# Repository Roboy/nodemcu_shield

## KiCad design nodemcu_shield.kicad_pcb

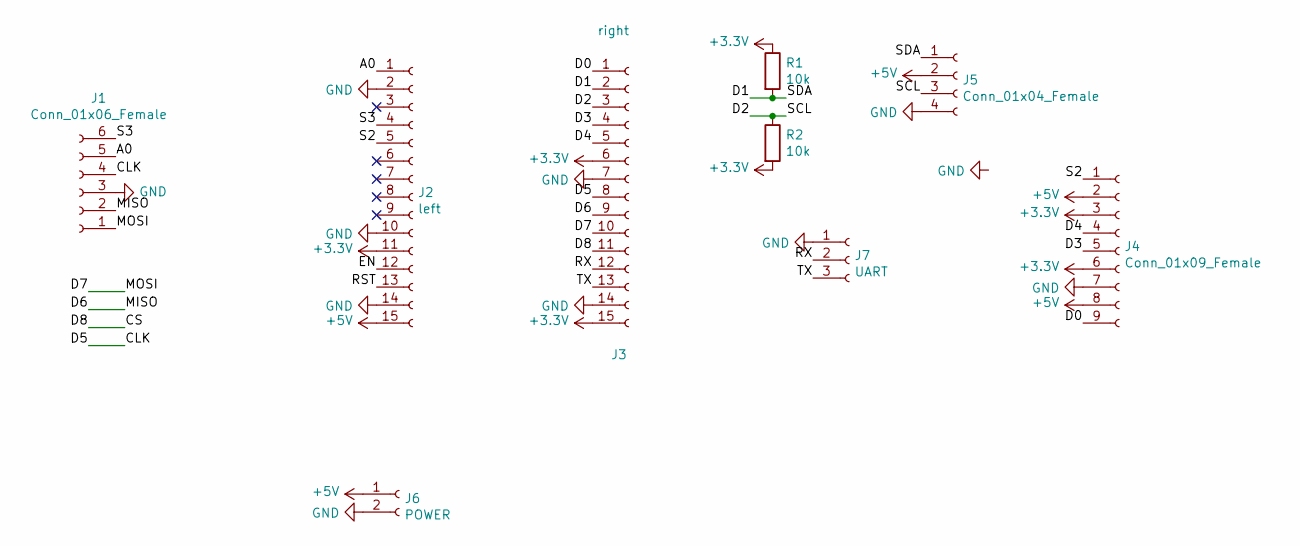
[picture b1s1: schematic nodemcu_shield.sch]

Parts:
J1: Conn_01x06_Female; TE-Connectivity_Micro-Match_connector_02x03_Pitch_1.27mm
J2: left; PinSocket_1x15_P2.54mm_Vertical
J3: right; PinSocket_1x15_P2.54mm_Vertical
J4: Conn_01x09_Female; PinHeader_1x09_P2.54mm_Horizontal
J5: Conn_01x04_Female; TE-Connectivity_Micro-Match_connector_02x02_Pitch_1.27mm
J6: POWER; Wago_2060_2_SMD
J7: UART; PinHeader_1x03_P2.54mm_Horizontal
R1, R2: 10k; R_0402_1005Metric

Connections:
+3V3: J2.11, J3.6, J3.15, J4.3, J4.6, R1.1, R2.2
+5V: J2.15, J4.2, J4.8, J5.2, J6.1
/A0: J1.5, J2.1
/CLK: J1.4, J3.8
/CS: J3.11
/D0: J3.1, J4.9
/D1: J3.2, J5.1, R1.2
/D2: J3.3, J5.3, R2.1
/D3: J3.4, J4.5
/D4: J3.5, J4.4
/D6: J1.2, J3.9
/D7: J1.1, J3.10
/EN: J2.12
/RST: J2.13
/RX: J3.12, J7.2
/S2: J2.5, J4.1
/S3: J1.6, J2.4
/TX: J3.13, J7.3
GND: J1.3, J2.2, J2.10, J2.14, J3.7, J3.14, J4.7, J5.4, J6.2, J7.1

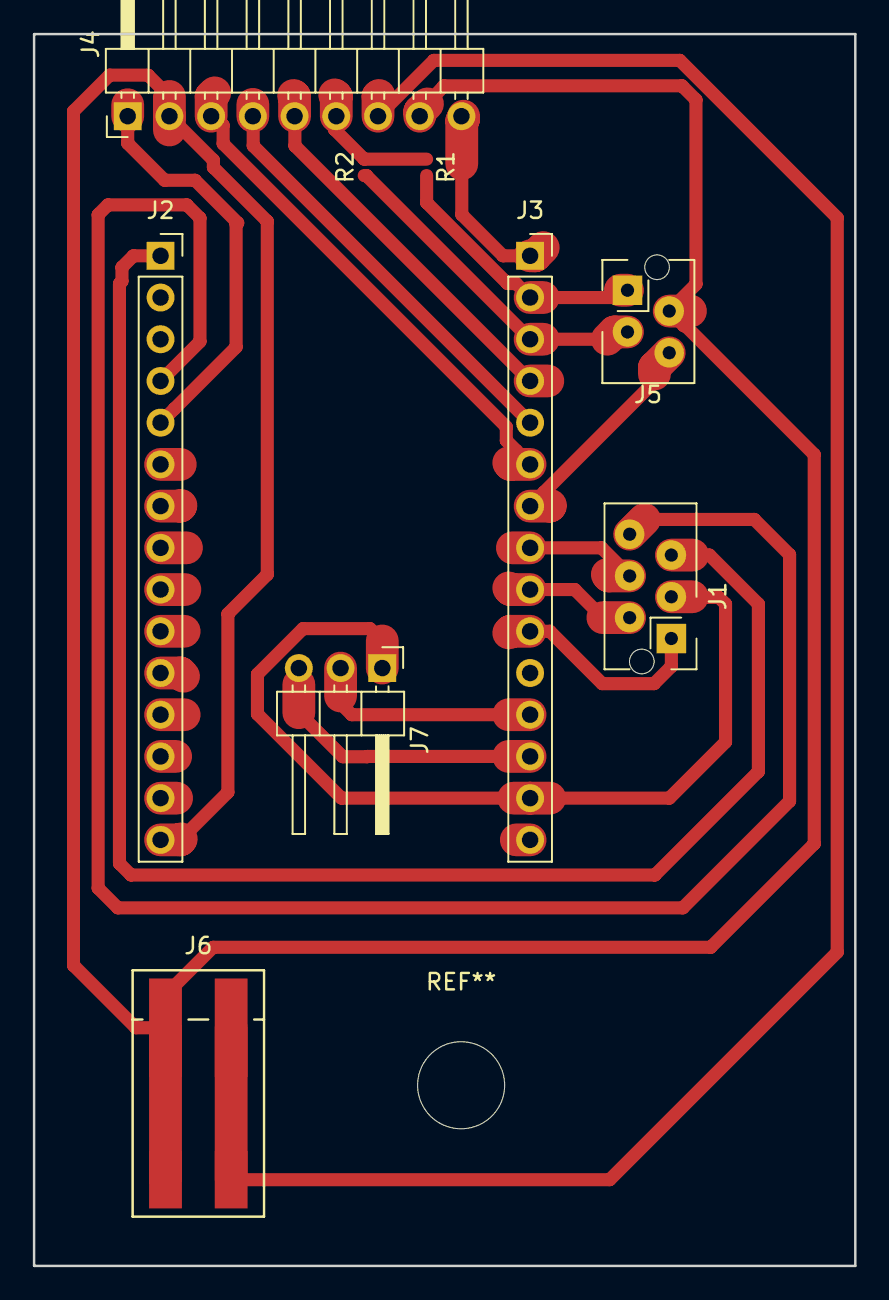
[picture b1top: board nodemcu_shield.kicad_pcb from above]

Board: 2 copper layers, 50.0 x 75.0 mm, 9 parts (0 on the bottom side), 16 nets.

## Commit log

2019-08-21 inital
2019-08-21 initial
